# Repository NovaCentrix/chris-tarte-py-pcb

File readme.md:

# The Tarte-Py

## Tester for Automatic Resistive Trace Experiments, in Python

## Revisions

### Version 1

First release. 

## Observations

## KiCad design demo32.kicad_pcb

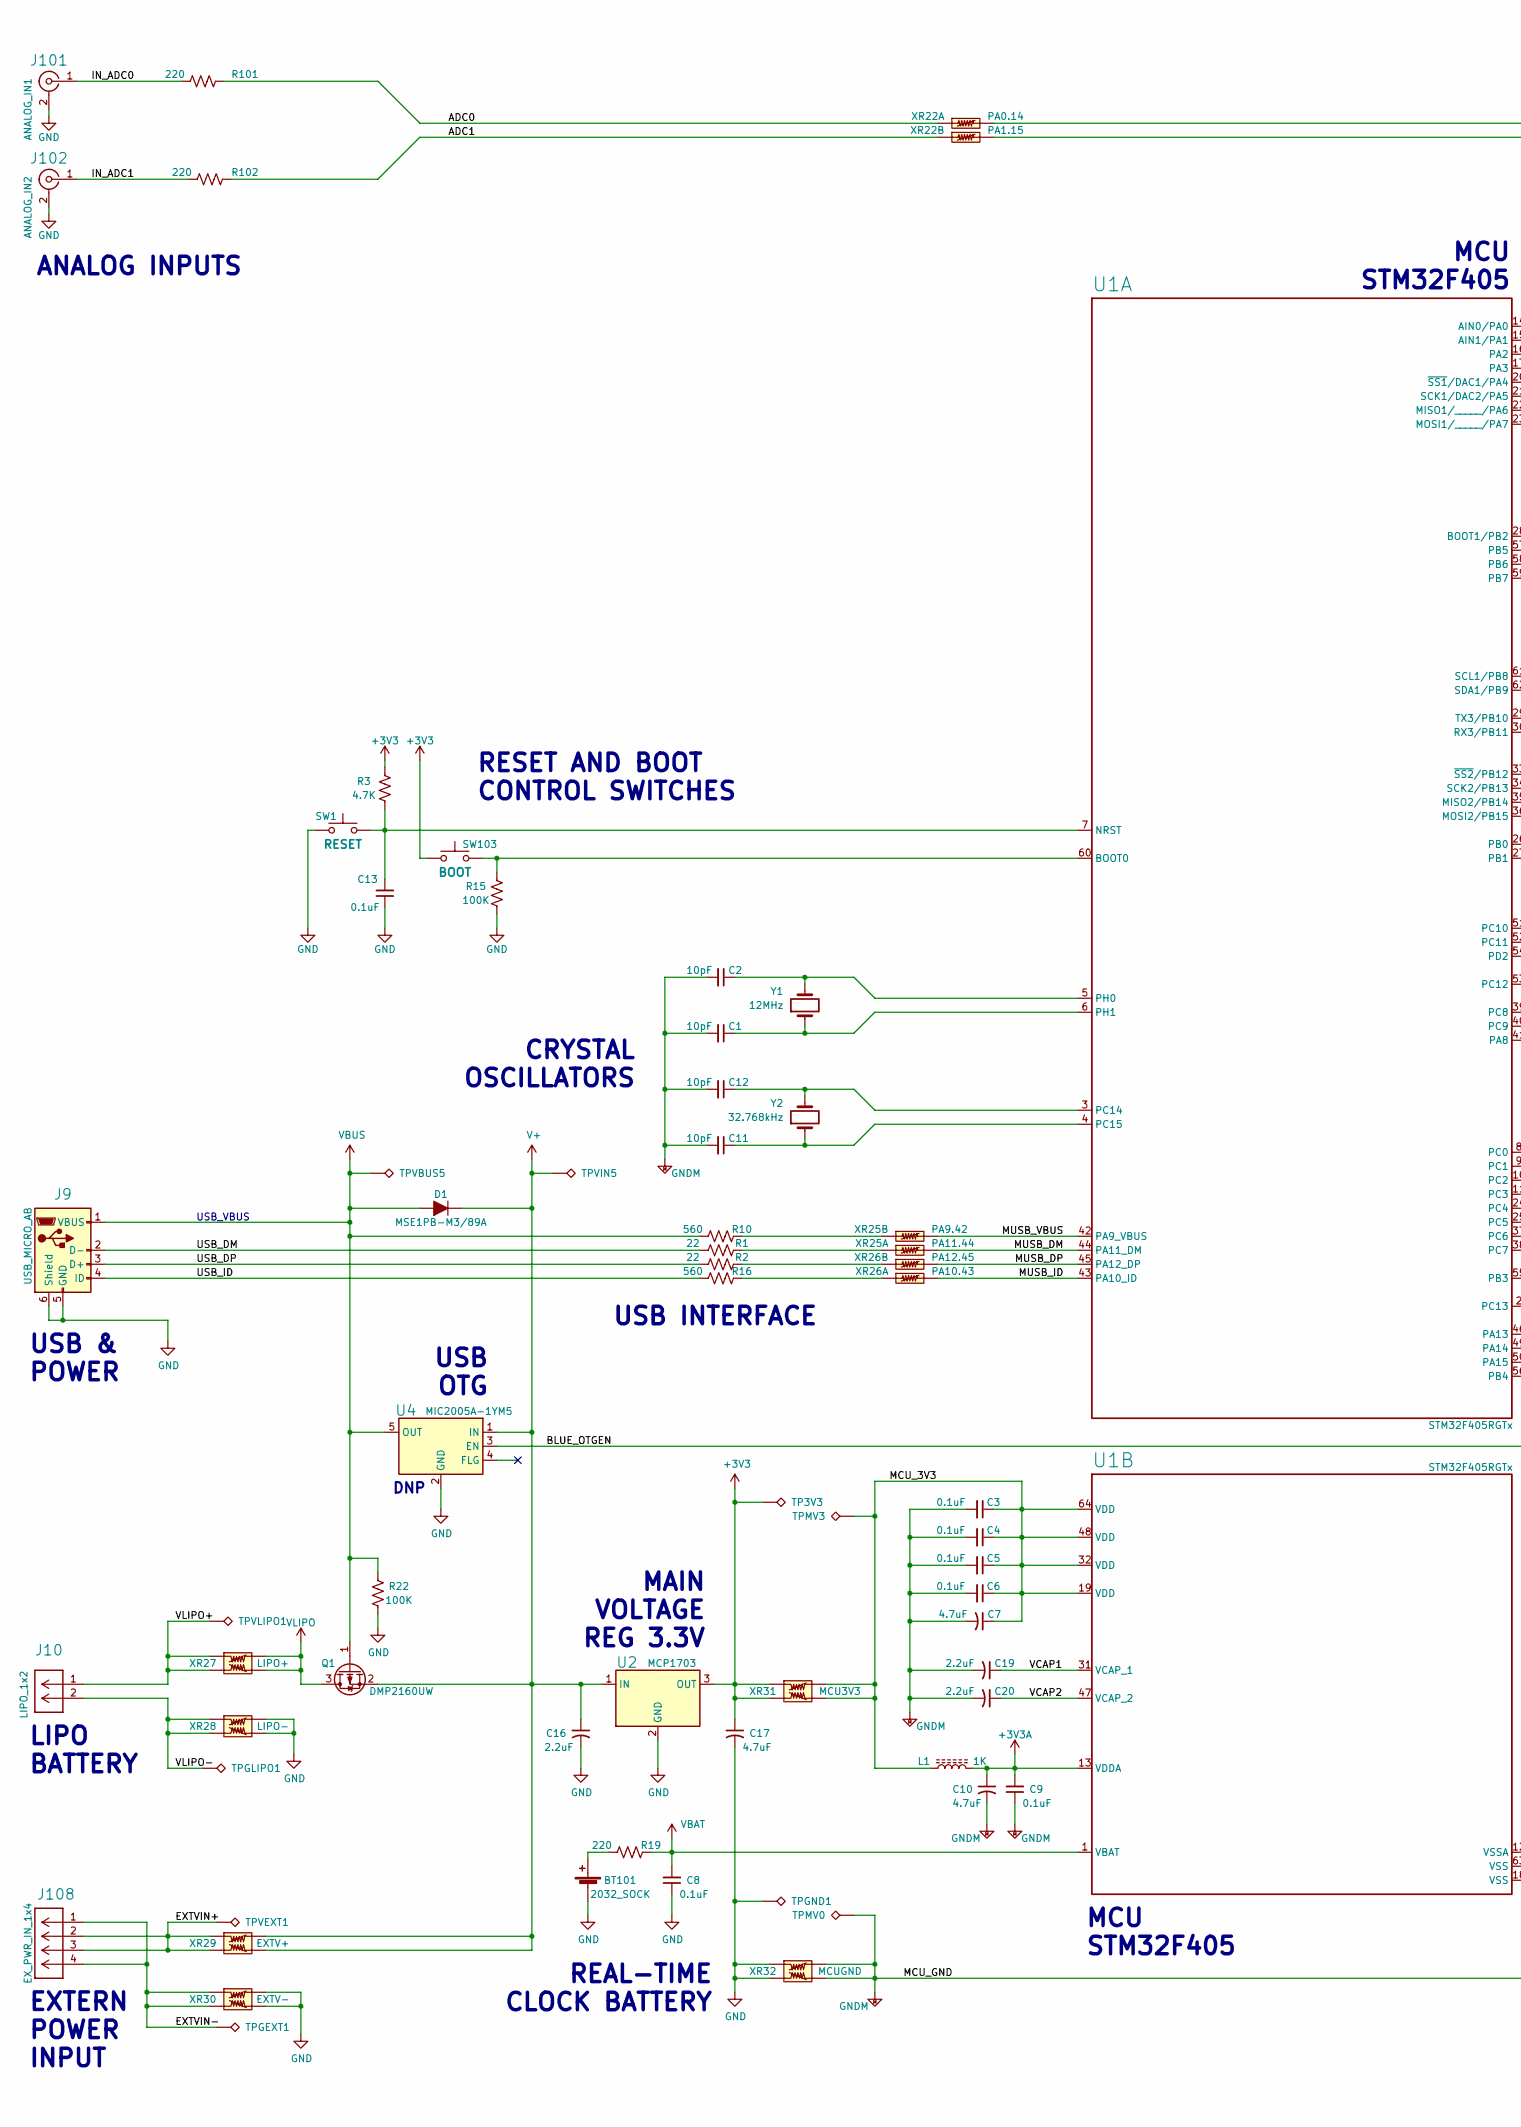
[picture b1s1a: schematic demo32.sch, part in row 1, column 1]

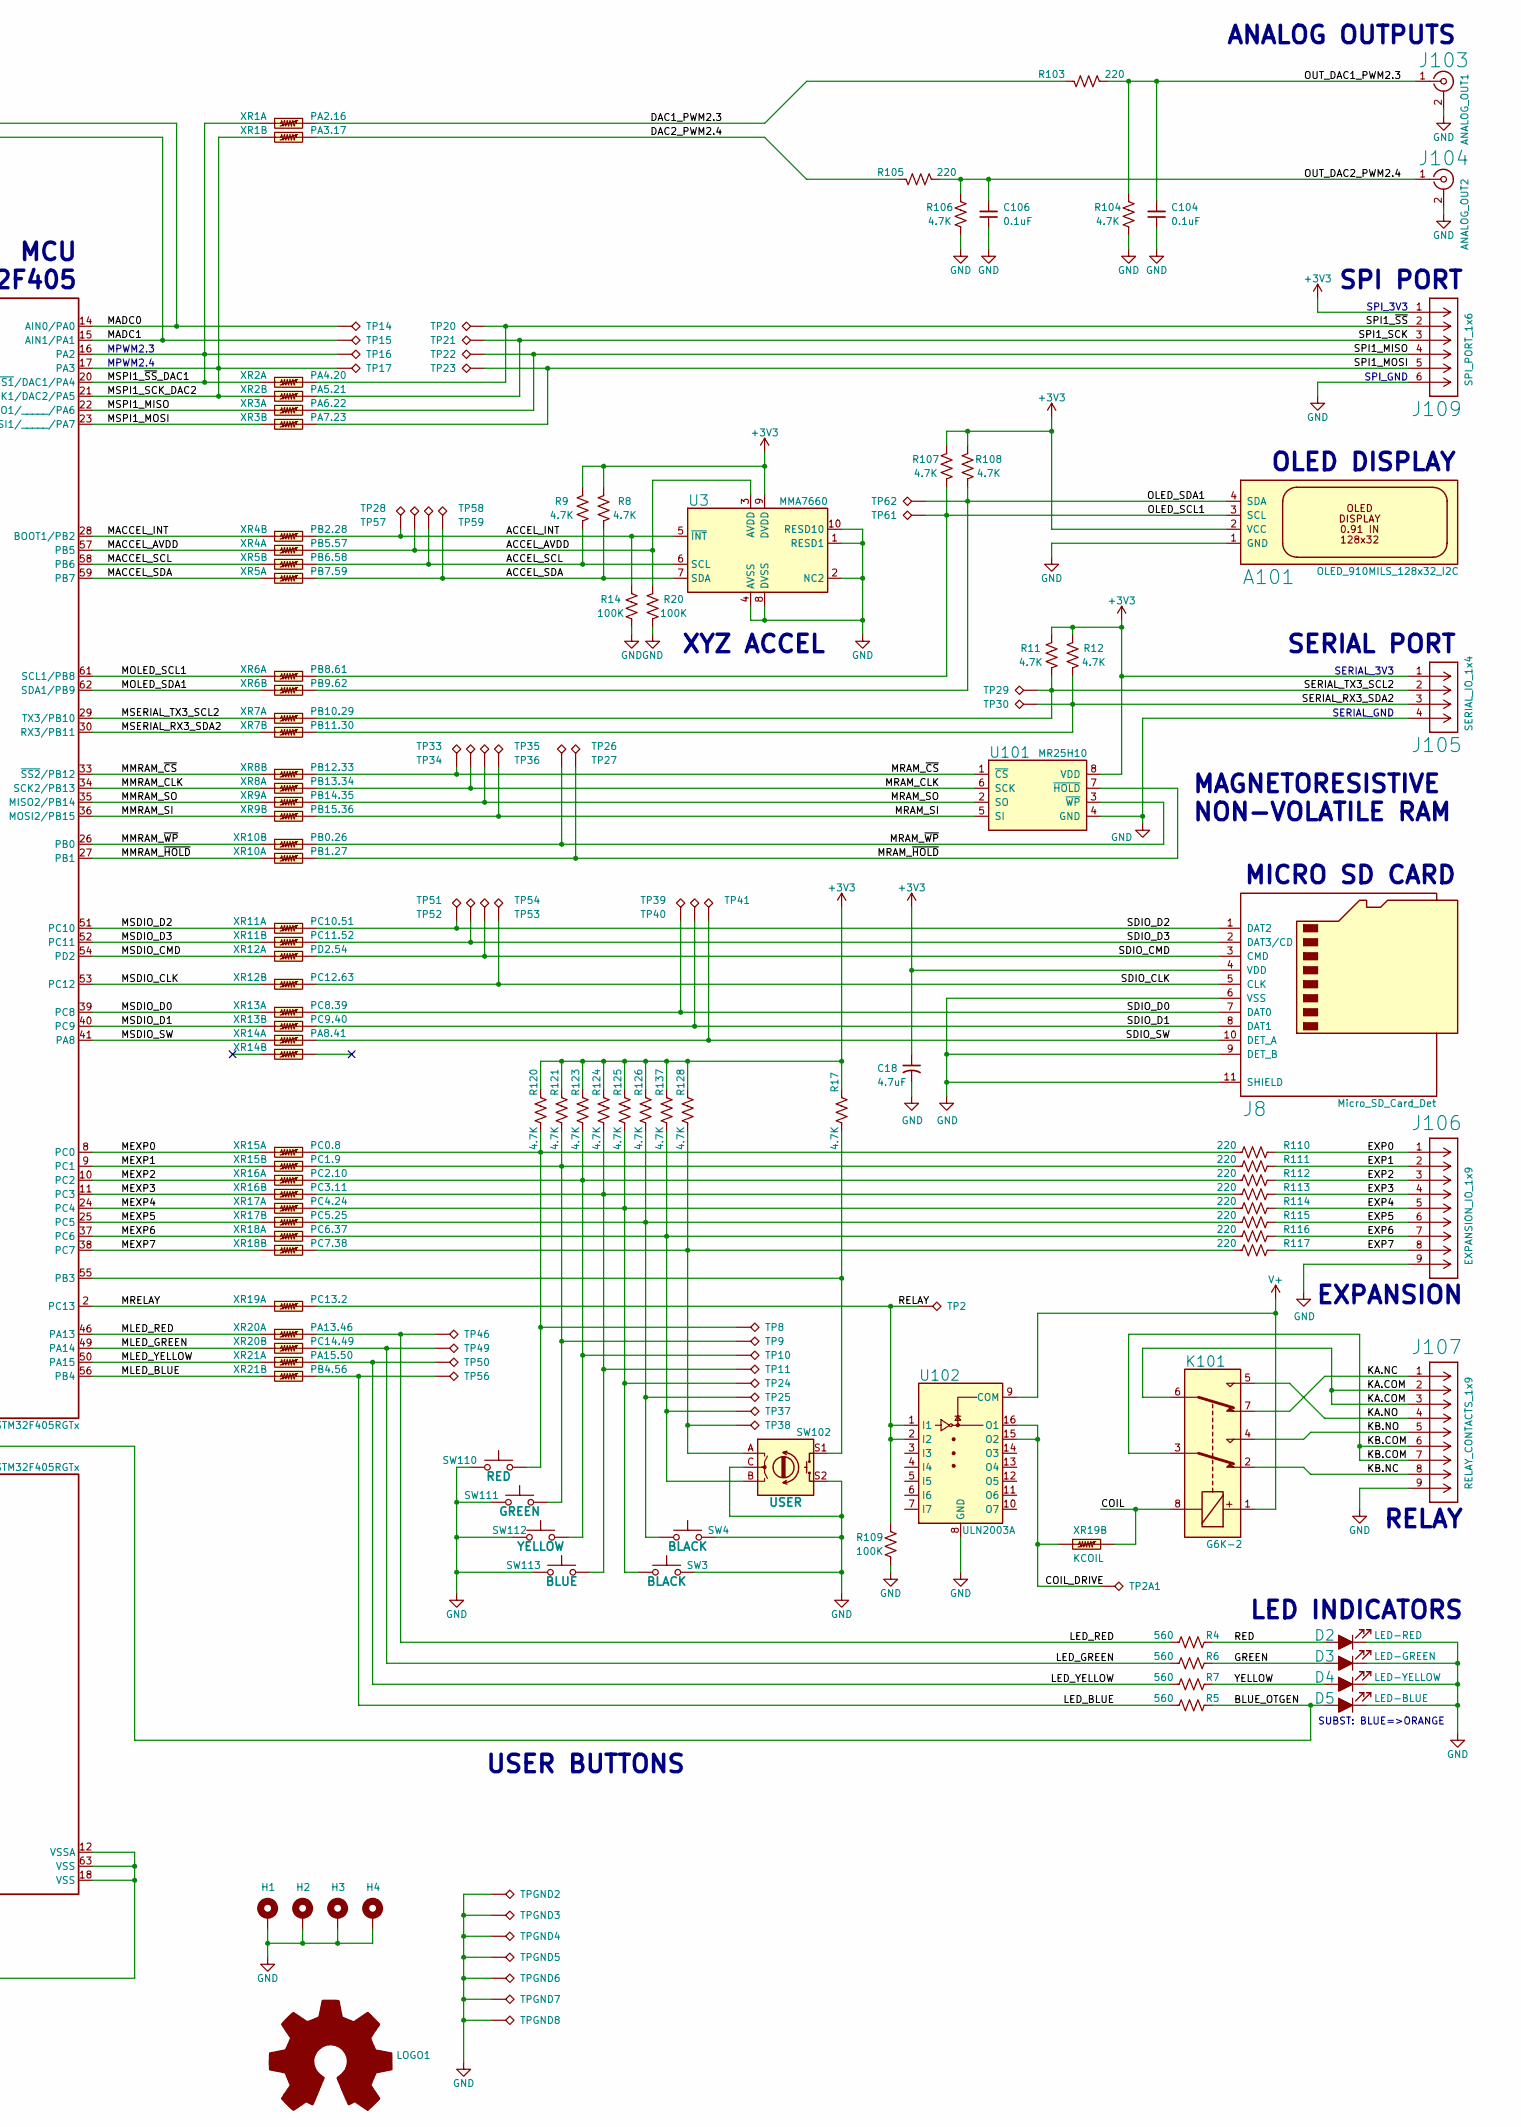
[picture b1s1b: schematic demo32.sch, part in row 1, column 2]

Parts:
A101: OLED_910MILS_128x32_I2C; MODULE_OLED_910
BT101: 2032_SOCK; BatteryHolder_Keystone_1059_1x2032
C1, C2, C11, C12: 10pF; C_0805_2012Metric
C3, C4, C5, C6, C8, C9, C13, C104, C106: 0.1uF; C_0805_2012Metric
C7, C10, C17, C18: 4.7uF; C_0805_2012Metric
C16, C19, C20: 2.2uF; C_0805_2012Metric
D1: MSE1PB-M3/89A; LED_0805_2012Metric_LiteOn_C171
D2: LED-RED; LED_0805_2012Metric_LiteOn_C171
D3: LED-GREEN; LED_0805_2012Metric_LiteOn_C171
D4: LED-YELLOW; LED_0805_2012Metric_LiteOn_C171
D5: LED-BLUE; LED_0805_2012Metric_LiteOn_C171
H1, H2, H3, H4: MountingHole_Pad; MountingHole_3.2mm_M3_ISO7380_Pad
J8: Micro_SD_Card_Det; microSD_HC_Hirose_DM3BT-DSF-PEJS
J9: USB_MICRO_AB; USB_Micro-AB_Molex_47590-0001
J10: LIPO_1x2; TE_640454-2-FLIP
J101: ANALOG_IN1; BNC_TEConnectivity_1634503_Vertical
J102: ANALOG_IN2; BNC_TEConnectivity_1634503_Vertical
J103: ANALOG_OUT1; BNC_TEConnectivity_1634503_Vertical
J104: ANALOG_OUT2; BNC_TEConnectivity_1634503_Vertical
J105: SERIAL_IO_1x4; TE_640454-4
J106: EXPANSION_IO_1x9; TE_640454-9
J107: RELAY_CONTACTS_1x9; TE_640454-9
J108: EX_PWR_IN_1x4; TE_640454-4_FLIP
J109: SPI_PORT_1x6; TE_640454-6
K101: G6K-2; Relay_DPDT_Omron_G6K-2F
L1: 1K; L_0805_2012Metric
LOGO1: Logo_Open_Hardware_Large; OSHW-Logo2_7.3x6mm_SilkScreen
Q1: DMP2160UW; SOT-23
R1, R2: 22; R_0805_2012Metric
R3, R8, R9, R11, R12, R17, R104, R106, R107, R108, R120, R121, R123, R124, R125, R126, R128, R137: 4.7K; R_0805_2012Metric
R4, R5, R6, R7, R10, R16: 560; R_0805_2012Metric
R14, R15, R20, R22, R109: 100K; R_0805_2012Metric
R19, R101, R102, R103, R105, R110, R111, R112, R113, R114, R115, R116, R117: 220; R_0805_2012Metric
SW1: RESET; SW_PUSH_6mm
SW3, SW4: BLACK; SW_PUSH_6mm
SW102: USER; RotaryEncoder_CTS_11CE
SW103: BOOT; SW_PUSH_6mm
SW110: RED; SW_PUSH_6mm
SW111: GREEN; SW_PUSH_6mm
SW112: YELLOW; SW_PUSH_6mm
SW113: BLUE; SW_PUSH_6mm
TP2, TP2A1, TP3V3, TP8, TP9, TP10, TP11, TP14, TP15, TP16, TP17, TP20, TP21, TP22, TP23, TP24, TP25, TP26, TP27, TP28, TP29, TP30, TP33, TP34, TP35, TP36, TP37, TP38, TP39, TP40, TP41, TP46, TP49, TP50, TP51, TP52, TP53, TP54, TP56, TP57, TP58, TP59, TP61, TP62: TestPoint; TestPoint_Keystone_5000-5004_Miniature
TPGEXT1: TestPoint; TestPoint_Keystone_5000-5004_Miniature
TPGLIPO1: TestPoint; TestPoint_Keystone_5000-5004_Miniature
TPGND1, TPGND2, TPGND3, TPGND4, TPGND5, TPGND6, TPGND7, TPGND8: TestPoint; TestPoint_Keystone_5000-5004_Miniature
TPMV0, TPMV3: TestPoint; TestPoint_Keystone_5000-5004_Miniature
TPVBUS5: TestPoint; TestPoint_Keystone_5000-5004_Miniature
TPVEXT1: TestPoint; TestPoint_Keystone_5000-5004_Miniature
TPVIN5: TestPoint; TestPoint_Keystone_5000-5004_Miniature
TPVLIPO1: TestPoint; TestPoint_Keystone_5000-5004_Miniature
U1: STM32F405RGTx; LQFP-64_10x10mm_P0.5mm
U2: MCP1703; SOT-223-3_TabPin2
U3: MMA7660; DFN-10_3x3mm_P0.5mm
U4: MIC2005A-1YM5; SOT-23-5
U101: MR25H10; DFN-8-1EP_6x5mm_P1.27mm_EP2x2mm
U102: ULN2003A; SOIC-16_3.9x9.9mm_P1.27mm
XR1, XR2, XR3, XR4, XR5, XR6, XR7, XR8, XR9, XR10, XR11, XR12, XR13, XR14, XR15, XR16, XR17, XR18, XR19, XR20, XR21, XR22, XR25, XR26: TRACER1; MODULE_TRACER
XR27, XR28, XR29, XR30, XR31, XR32: TRACER2; MODULE_TRACER
Y1: 12MHz; Crystal_SMD_Abracon_ABM7-2Pin_6.0x3.5mm
Y2: 32.768kHz; Crystal_C26-LF_D2.1mm_L6.5mm_Horizontal_1EP_style1

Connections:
+3V3: A101.2 (VCC), C17.1, C18.1, J8.4 (VDD), J105.1, J109.1, R3.1, R8.1, R9.2, R11.2, R12.1, R17.1, R107.2, R108.1, R120.1, R121.1, R123.1, R124.1, R125.1, R126.1, R128.1, R137.1, SW103.1, TP3V3.1, U2.3 (OUT), U3.9 (DVDD), U101.8 (VDD), XR31.1, XR31.3
+3V3A: C9.2, C10.1, L1.2, U1.13 (VDDA)
/ACCEL_AVDD: R20.1, TP57.1, U3.3 (AVDD), XR4.2
/ACCEL_INT: R14.1, TP28.1, U3.5 (~INT), XR4.4
/ACCEL_SCL: R9.1, TP58.1, U3.6 (SCL), XR5.4
/ACCEL_SDA: R8.2, TP59.1, U3.7 (SDA), XR5.2
/ADC0: R101.1, XR22.1
/ADC1: R102.1, XR22.3
/BLUE_OTGEN: D5.1 (A), R5.1, U4.3 (EN)
/COIL: K101.8, XR19.4
/COIL_DRIVE: TP2A1.1, U102.15 (O2), U102.16 (O1), XR19.3
/DAC1_PWM2.3: R103.1, XR1.2
/DAC2_PWM2.4: R105.1, XR1.4
/EXP0: J106.1, R110.1
/EXP1: J106.2, R111.1
/EXP2: J106.3, R112.1
/EXP3: J106.4, R113.1
/EXP4: J106.5, R114.1
/EXP5: J106.6, R115.1
/EXP6: J106.7, R116.1
/EXP7: J106.8, R117.1
/EXTVIN+: J108.2, J108.3, TPVEXT1.1, XR29.1, XR29.3
/EXTVIN-: J108.1, J108.4, TPGEXT1.1, XR30.1, XR30.3
/GREEN: D3.1 (A), R6.1
/IN_ADC0: J101.1 (In), R101.2
/IN_ADC1: J102.1 (In), R102.2
/KA.COM: J107.2, J107.3, K101.6
/KA.NC: J107.1, K101.7
/KA.NO: J107.4, K101.5
/KB.COM: J107.6, J107.7, K101.3
/KB.NC: J107.8, K101.2
/KB.NO: J107.5, K101.4
/LED_BLUE: R5.2, TP56.1, XR21.4
/LED_GREEN: R6.2, TP49.1, XR20.4
/LED_RED: R4.2, TP46.1, XR20.2
/LED_YELLOW: R7.2, TP50.1, XR21.2
/MACCEL_AVDD: U1.57 (PB5), XR4.1
/MACCEL_INT: U1.28 (BOOT1/PB2), XR4.3
/MACCEL_SCL: U1.58 (PB6), XR5.3
/MACCEL_SDA: U1.59 (PB7), XR5.1
/MADC0: TP14.1, U1.14 (AIN0/PA0), XR22.2
/MADC1: TP15.1, U1.15 (AIN1/PA1), XR22.4
/MCU_3V3: C3.1, C4.1, C5.1, C6.1, C7.1, L1.1, TPMV3.1, U1.19 (VDD), U1.32 (VDD), U1.48 (VDD), U1.64 (VDD), XR31.2, XR31.4
/MEXP0: U1.8 (PC0), XR15.1
/MEXP1: U1.9 (PC1), XR15.3
/MEXP2: U1.10 (PC2), XR16.1
/MEXP3: U1.11 (PC3), XR16.3
/MEXP4: U1.24 (PC4), XR17.1
/MEXP5: U1.25 (PC5), XR17.3
/MEXP6: U1.37 (PC6), XR18.1
/MEXP7: U1.38 (PC7), XR18.3
/MLED_BLUE: U1.56 (PB4), XR21.3
/MLED_GREEN: U1.49 (PA14), XR20.3
/MLED_RED: U1.46 (PA13), XR20.1
/MLED_YELLOW: U1.50 (PA15), XR21.1
/MMRAM_CLK: U1.34 (SCK2/PB13), XR8.1
/MMRAM_SI: U1.36 (MOSI2/PB15), XR9.3
/MMRAM_SO: U1.35 (MISO2/PB14), XR9.1
/MMRAM_~CS: U1.33 (~SS2~/PB12), XR8.3
/MMRAM_~HOLD: U1.27 (PB1), XR10.1
/MMRAM_~WP: U1.26 (PB0), XR10.3
/MOLED_SCL1: U1.61 (SCL1/PB8), XR6.1
/MOLED_SDA1: U1.62 (SDA1/PB9), XR6.3
/MRAM_CLK: TP34.1, U101.6 (SCK), XR8.2
/MRAM_SI: TP36.1, U101.5 (SI), XR9.4
/MRAM_SO: TP35.1, U101.2 (SO), XR9.2
/MRAM_~CS: TP33.1, U101.1 (~CS), XR8.4
/MRAM_~HOLD: TP27.1, U101.7 (~HOLD), XR10.2
/MRAM_~WP: TP26.1, U101.3 (~WP), XR10.4
/MRELAY: U1.2 (PC13), XR19.1
/MSDIO_CLK: U1.53 (PC12), XR12.3
/MSDIO_CMD: U1.54 (PD2), XR12.1
/MSDIO_D0: U1.39 (PC8), XR13.1
/MSDIO_D1: U1.40 (PC9), XR13.3
/MSDIO_D2: U1.51 (PC10), XR11.1
/MSDIO_D3: U1.52 (PC11), XR11.3
/MSDIO_SW: U1.41 (PA8), XR14.1
/MSERIAL_RX3_SDA2: U1.30 (RX3/PB11), XR7.3
/MSERIAL_TX3_SCL2: U1.29 (TX3/PB10), XR7.1
/MSPI1_MISO: U1.22 (MISO1/_____/PA6), XR3.1
/MSPI1_MOSI: U1.23 (MOSI1/_____/PA7), XR3.3
/MSPI1_SCK_DAC2: TP17.1, U1.17 (PA3), U1.21 (SCK1/DAC2/PA5), XR1.3, XR2.3
/MSPI1_~SS~_DAC1: TP16.1, U1.16 (PA2), U1.20 (~SS1~/DAC1/PA4), XR1.1, XR2.1
/MUSB_DM: U1.44 (PA11_DM), XR25.2
/MUSB_DP: U1.45 (PA12_DP), XR26.4
/MUSB_ID: U1.43 (PA10_ID), XR26.2
/MUSB_VBUS: U1.42 (PA9_VBUS), XR25.4
/OLED_SCL1: A101.3 (SCL), R107.1, TP61.1, XR6.2
/OLED_SDA1: A101.4 (SDA), R108.2, TP62.1, XR6.4
/OUT_DAC1_PWM2.3: C104.2, J103.1 (In), R103.2, R104.1
/OUT_DAC2_PWM2.4: C106.2, J104.1 (In), R105.2, R106.1
/RED: D2.1 (A), R4.1
/RELAY: R109.1, TP2.1, U102.1 (I1), U102.2 (I2), XR19.2
/SDIO_CLK: J8.5 (CLK), TP53.1, XR12.4
/SDIO_CMD: J8.3 (CMD), TP54.1, XR12.2
/SDIO_D0: J8.7 (DAT0), TP39.1, XR13.2
/SDIO_D1: J8.8 (DAT1), TP40.1, XR13.4
/SDIO_D2: J8.1 (DAT2), TP51.1, XR11.2
/SDIO_D3: J8.2 (DAT3/CD), TP52.1, XR11.4
/SDIO_SW: J8.10 (DET_A), TP41.1, XR14.2
/SERIAL_RX3_SDA2: J105.3, R12.2, TP30.1, XR7.4
/SERIAL_TX3_SCL2: J105.2, R11.1, TP29.1, XR7.2
/SPI1_MISO: J109.4, TP22.1, XR3.2
/SPI1_MOSI: J109.5, TP23.1, XR3.4
/SPI1_SCK: J109.3, TP21.1, XR2.4
/SPI1_~SS: J109.2, TP20.1, XR2.2
/USB_DM: J9.2 (D-), R1.2
/USB_DP: J9.3 (D+), R2.2
/USB_ID: J9.4 (ID), R16.2
/VCAP1: C19.1, U1.31 (VCAP_1)
/VCAP2: C20.1, U1.47 (VCAP_2)
/VLIPO+: J10.1, TPVLIPO1.1, XR27.1, XR27.3
/VLIPO-: J10.2, TPGLIPO1.1, XR28.1, XR28.3
/YELLOW: D4.1 (A), R7.1
GND: A101.1 (GND), BT101.1 (-), C8.1, C13.1, C16.2, C17.2, C18.2, C104.1, C106.1, D2.2 (K), D3.2 (K), D4.2 (K), D5.2 (K), H1.1, H2.1, H3.1, H4.1, J8.6 (VSS), J8.9 (DET_B), J8.11 (SHIELD), J9.5 (GND), J9.6 (Shield), J101.2 (Ext), J102.2 (Ext), J103.2 (Ext), J104.2 (Ext), J105.4, J106.9, J107.9, J109.6, R14.2, R15.2, R20.2, R22.2, R104.2, R106.2, R109.2, SW1.1, SW3.1, SW4.1, SW102.C, SW102.S2, SW110.1, SW111.1, SW112.1, SW113.1, TPGND1.1, TPGND2.1, TPGND3.1, TPGND4.1, TPGND5.1, TPGND6.1, TPGND7.1, TPGND8.1, U2.2 (GND), U3.1 (RESD1), U3.2 (NC2), U3.4 (AVSS), U3.8 (DVSS), U3.10 (RESD10), U4.2 (GND), U101.4 (GND), U102.8 (GND), XR28.2, XR28.4, XR30.2, XR30.4, XR32.1, XR32.3
GNDM: C1.2, C2.2, C3.2, C4.2, C5.2, C6.2, C7.2, C9.1, C10.2, C11.2, C12.2, C19.2, C20.2, TPMV0.1, U1.12 (VSSA), U1.18 (VSS), U1.63 (VSS), XR32.2, XR32.4
unnamed: BT101.2 (+), BT101.3 (+), R19.2
unnamed: C1.1, U1.6 (PH1), Y1.1
unnamed: C2.1, U1.5 (PH0), Y1.2
unnamed: C11.1, U1.4 (PC15), Y2.1
unnamed: C12.1, U1.3 (PC14), Y2.2
unnamed: C13.2, R3.2, SW1.2, U1.7 (NRST)
unnamed: R1.1, XR25.1
unnamed: R2.1, XR26.3
unnamed: R10.1, XR25.3
unnamed: R15.1, SW103.2, U1.60 (BOOT0)
unnamed: R16.1, XR26.1
unnamed: R17.2, SW102.S1, U1.55 (PB3)
unnamed: R110.2, R120.2, SW110.2, TP8.1, XR15.2
unnamed: R111.2, R121.2, SW111.2, TP9.1, XR15.4
unnamed: R112.2, R123.2, SW112.2, TP10.1, XR16.2
unnamed: R113.2, R124.2, SW113.2, TP11.1, XR16.4
unnamed: R114.2, R125.2, SW3.2, TP24.1, XR17.2
unnamed: R115.2, R126.2, SW4.2, TP25.1, XR17.4
unnamed: R116.2, R137.2, SW102.B, TP37.1, XR18.2
unnamed: R117.2, R128.2, SW102.A, TP38.1, XR18.4
V+: C16.1, D1.1 (K), K101.1, Q1.2 (S), TPVIN5.1, U2.1 (IN), U4.1 (IN), U102.9 (COM), XR29.2, XR29.4
VBAT: C8.2, R19.1, U1.1 (VBAT)
VBUS: D1.2 (A), J9.1 (VBUS), Q1.1 (G), R10.2, R22.1, TPVBUS5.1, U4.5 (OUT)
VLIPO: Q1.3 (D), XR27.2, XR27.4

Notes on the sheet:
USB_VBUS
DNP
SERIAL_3V3
SERIAL_GND
ANALOG INPUTS
ANALOG OUTPUTS
OLED DISPLAY
SERIAL PORT
MICRO SD CARD
EXPANSION
RELAY
LED INDICATORS
USER BUTTONS
XYZ ACCEL
MAGNETORESISTIVE NON-VOLATILE RAM
RESET AND BOOT CONTROL SWITCHES
CRYSTAL OSCILLATORS
USB INTERFACE
USB OTG
LIPO BATTERY
EXTERN POWER INPUT
USB & POWER
REAL-TIME CLOCK BATTERY
MAIN VOLTAGE REG 3.3V
MCU STM32F405
SPI_3V3
SPI_GND
MPWM2.3
MPWM2.4
SUBST: BLUE=>ORANGE
SPI PORT

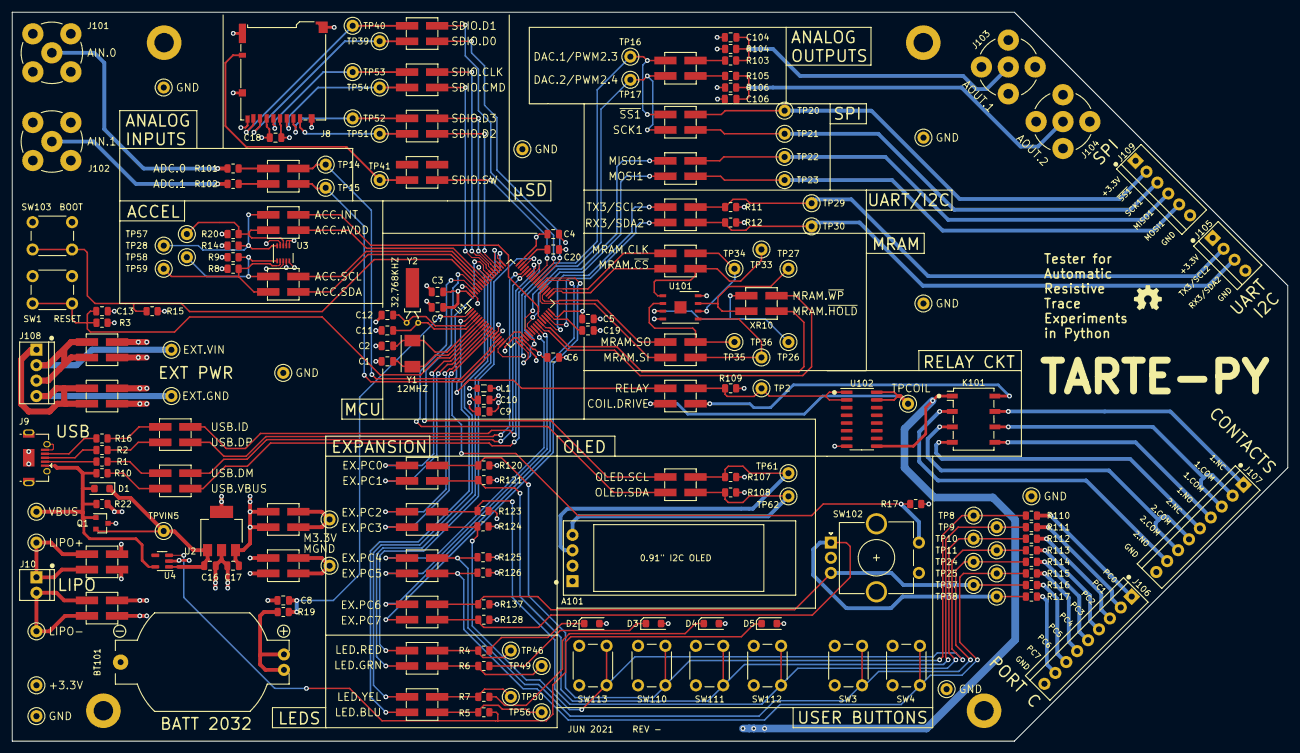
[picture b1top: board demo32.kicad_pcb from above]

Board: 4 copper layers, 210.0 x 120.0 mm, 198 parts (0 on the bottom side), 140 nets.

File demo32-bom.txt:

Reference, Quantity, Value, Footprint, Datasheet
A101 ,1,"OLED_910MILS_128x32_I2C","",""
BT101 ,1,"2032_SOCK","","~"
C16 C19 C20 ,3,"2.2uF","","~"
C7 C10 C17 C18 ,4,"4.7uF","","~"
C1 C2 C11 C12 ,4,"10pF","",""
C3 C4 C5 C6 C8 C9 C13 C104 C106 ,9,"0.1uF","",""
D1 ,1,"MSE1PB-M3/89A","",""
D2 ,1,"LED-RED","",""
D3 ,1,"LED-GREEN","",""
D4 ,1,"LED-YELLOW","",""
D5 ,1,"LED-BLUE","",""
J10 ,1,"LIPO_BATTERY","",""
J101 ,1,"ANALOG_IN1",""," ~"
J102 ,1,"ANALOG_IN2",""," ~"
J103 ,1,"ANALOG_OUT1",""," ~"
J104 ,1,"ANALOG_OUT2",""," ~"
J105 ,1,"SERIAL_IO","",""
J106 ,1,"EXPANSION_IO","",""
J107 ,1,"RELAY_CONTACTS","",""
J108 ,1,"EXT_POWER_IN","",""
J8 ,1,"Micro_SD_Card_Det","","https://www.hirose.com/product/en/download_file/key_name/DM3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"
J9 ,1,"USB_TYPE_B_MICRO","","~"
K101 ,1,"G6K-2","",""
L1 ,1,"1K","","~"
Q1 ,1,"BSS84","Package_TO_SOT_SMD:SOT-23","http://assets.nexperia.com/documents/data-sheet/BSS84.pdf"
R1 R2 ,2,"22","",""
R4 R5 R6 R7 R10 R16 ,6,"560","",""
R3 R8 R9 R11 R12 R17 R104 R106 R107 R108 R120 R121 R123 R124 R125 R126 R128 R137 ,18,"4.7K","",""
R19 R101 R102 R103 R105 R110 R111 R112 R113 R114 R115 R116 R117 ,13,"220","",""
R14 R15 R20 R22 R109 ,5,"100K","",""
SW1 ,1,"RESET","","~"
SW103 ,1,"BOOT","","~"
SW110 ,1,"RED","","~"
SW111 ,1,"GREEN","","~"
SW112 ,1,"YELLOW","","~"
SW113 ,1,"BLUE","","~"
SW2 ,1,"USER","","~"
SW3 SW4 SW5 SW6 ,4,"BLACK","","~"
TPMV0 TPGND1 TPVLIPO1 TPGLIPO1 TPVEXT1 TPGEXT1 TP2 TPMV3 TPVBUS5 TPVIN5 TP8 TP9 TP10 TP11 TP14 TP15 TP16 TP17 TP2A1 TP22 TP23 TP24 TP25 TP26 TP27 TP29 TP30 TP33 TP3V3 TP34 TP35 TP36 TP37 TP38 TP39 TP40 TP41 TP46 TP49 TP50 TP51 TP52 TP53 TP54 TP56 TP61 TP62 ,47,"TestPoint","",""
U1 ,1,"STM32F405RGTx","Package_QFP:LQFP-64_10x10mm_P0.5mm","http://www.st.com/st-web-ui/static/active/en/resource/techni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"
U101 ,1,"MR25H10","",""
U102 ,1,"ULN2003A","",""
U2 ,1,"MCP1703","",""
U3 ,1,"MMA7660","Package_DFN_QFN:DFN-10_2x2mm_P0.4mm","http://cache.freescale.com/files/sensors/doc/data_sheet/MMA8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"
U4 ,1,"MIC2005A-1YM5","",""
XR2 XR3 XR4 XR5 XR6 XR8 XR9 XR10 XR11 XR14 XR15 XR20 XR21 XR24 XR25 XR26 XR27 XR28 XR29 XR30 XR33 XR34 XR35 XR36 XR37 XR38 XR39 XR40 XR41 XR42 XR43 XR44 XR45 XR46 XR49 XR50 XR51 XR52 XR53 XR54 XR56 XR57 XR58 XR59 XR61 XR62 XR1021 ,47,"TRACER1","",""
XRV0 XRV3 XR101 XR102 XR1081 XR1082 ,6,"TRACER2","",""
Y1 ,1,"12MHz","","~"
Y2 ,1,"32.768kHz","","~"

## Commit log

2021-06-10 initial release
2021-06-14 updated one datasheet
2021-06-14 documentation cleanup, one local project library
2021-06-15 Making BOM
